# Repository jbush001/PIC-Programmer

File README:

This is a programmer for PIC microcontrollers I built a while ago.

parallel_port_programmer: This is the first programmer I built.
It uses a 3rd party library called DlPortIo that allows user space programmers 
to execute IN/OUT instructions.  It bit bangs data over the parallel port.
It is difficult to get microsecond accurate timing, so I ended up using fairly
large granularity delays.  As a result, it was really slow.

serial_port_programmer: This uses a PIC to drive the programming lines,
so a programmer is required to bootstrap it.  The programmer PIC communicates
with the host computer using a serial port.  I prototyped the first version
on a piece of perf board with point-to-point connections.  The schematic
is captured in serial-programmer.sch. I also design a version that would use
a USB-to-serial converter and was bus powered, but never built it.

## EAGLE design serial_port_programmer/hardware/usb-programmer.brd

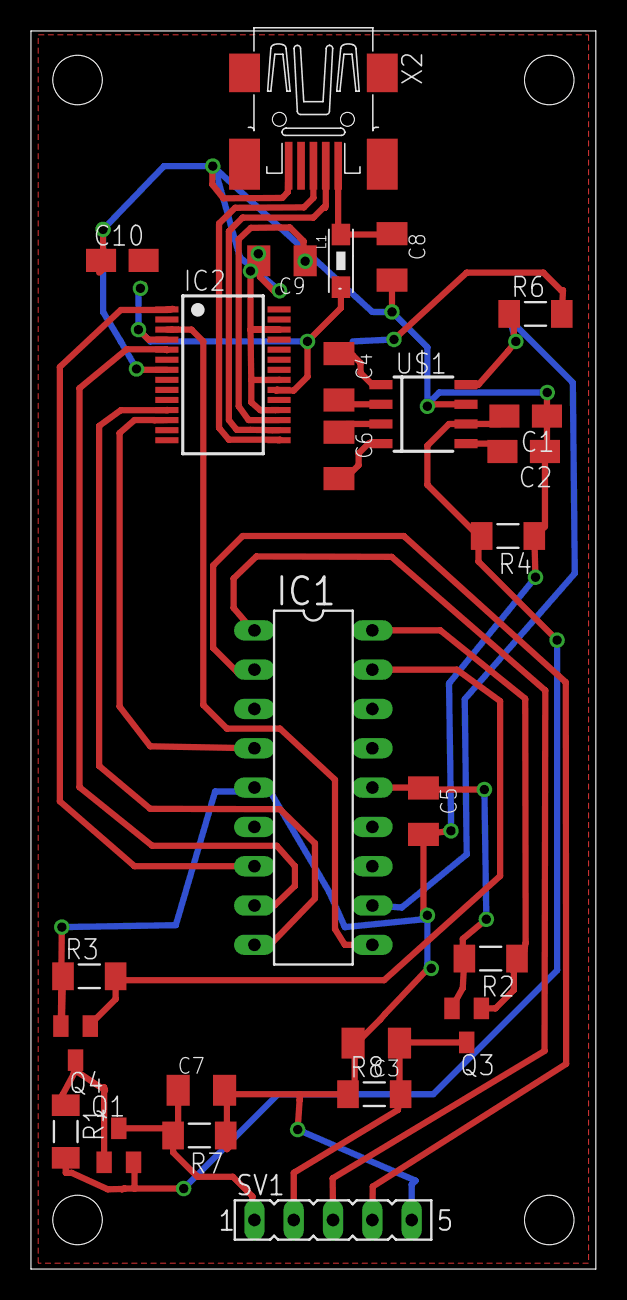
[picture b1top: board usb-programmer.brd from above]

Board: 2 copper layers, 36.5 x 80.0 mm, 26 parts (0 on the bottom side), 24 nets.

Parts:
C1, C2: A/3216-18R
C3, C4, C5, C6, C7: C1206K
C8: 10nF; C1206K
C9: 100 nF; C1206K
C10: 4.7 uF; A/3216-18R
IC1: PIC16F84AP; DIL18
IC2: FT232RL; SSOP28
L1: 1210
Q1, Q3: BSS84; SOT23
Q4: BSS123; SOT23
R1, R2, R3, R7, R8: 100k; M1406
R4: 1M; M1406
R6: 10k; M1406
SV1: FE05-1
U$1: LT1262; SOIC8
X2: MINI-USB-32005-201; 32005-201

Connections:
5VPOWER: C2.+, C5.1, C10.+, IC1.14, IC2.4, IC2.20, L1.2, Q3.2, R2.2, R6.2, U$1.5
GND: C1.-, C2.-, C3.2, C5.2, C7.2, C8.2, C9.2, C10.-, IC1.5, IC2.7, IC2.18, IC2.21, IC2.25, IC2.26, Q4.2, R3.1, R4.1, R7.1, R8.1, SV1.5, U$1.7, X2.5
HOST_TO_PROG: IC1.7, IC2.1
unnamed: IC1.2, SV1.4
unnamed: IC1.1, SV1.3
unnamed: IC1.17, Q4.1, R3.2
unnamed: Q1.1, Q4.3, R1.1
unnamed: C1.+, Q1.2, R1.2, R4.2, U$1.6
unnamed: IC1.18, Q3.1, R2.1
unnamed: C3.1, Q3.3, R8.2, SV1.2
unnamed: C9.1, IC2.17
unnamed: C6.1, U$1.3
unnamed: C7.1, Q1.3, R7.2, SV1.1
unnamed: C4.2, U$1.2
unnamed: C4.1, U$1.1
unnamed: C6.2, U$1.4
unnamed: IC1.9, IC2.11
unnamed: IC1.4, IC2.12
unnamed: IC1.10, IC2.3
unnamed: C8.1, L1.1, X2.1
unnamed: IC1.11, R6.1, U$1.8
PROG_TO_HOST: IC1.8, IC2.5
USB_DMINUS: IC2.16, X2.2
USB_DPLUS: IC2.15, X2.3

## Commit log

2012-07-23 Add license header
2013-08-23 Add schematic images
2013-08-23 Add board art.
2019-01-07 Create LICENSE
